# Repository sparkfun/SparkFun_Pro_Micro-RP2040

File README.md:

SparkFun Pro Micro RP2040
========================================

[*SparkFun Pro Micro RP2040 (DEV-17717)*](https://www.sparkfun.com/products/17717)

The SparkFun Pro Micro RP2040 is a low-cost, high performance board with flexible digital interfaces featuring the Raspberry Pi Foundation's RP2040 microcontroller. Besides the good 'ol Pro Micro footprint, the board also includes a WS2812B addressable LED, boot button, reset button, Qwiic connector, USB-C, resettable PTC fuse, and castellated pads.

Repository Contents
-------------------

* **/Hardware** - All Eagle design files (.brd, .sch, .STL)

Documentation
--------------

* **[Hookup Guide](https://learn.sparkfun.com/tutorials/1560)** - Basic hookup guide for the Pro Micro RP2040
* **[SparkFun Graphical Datasheets](https://github.com/sparkfun/Graphical_Datasheets)** - Graphical datasheets for various SparkFun products.

Product Versions
----------------

* [DEV-17717](https://www.sparkfun.com/products/17717)- initial release

License Information
-------------------

This product is _**open source**_! 

Please review the LICENSE.md file for license information. 

If you have any questions or concerns on licensing, please contact technical support on our [SparkFun forums](https://forum.sparkfun.com/viewforum.php?f=152).

Distributed as-is; no warranty is given.

- Your friends at SparkFun.

_<COLLABORATION CREDIT>_

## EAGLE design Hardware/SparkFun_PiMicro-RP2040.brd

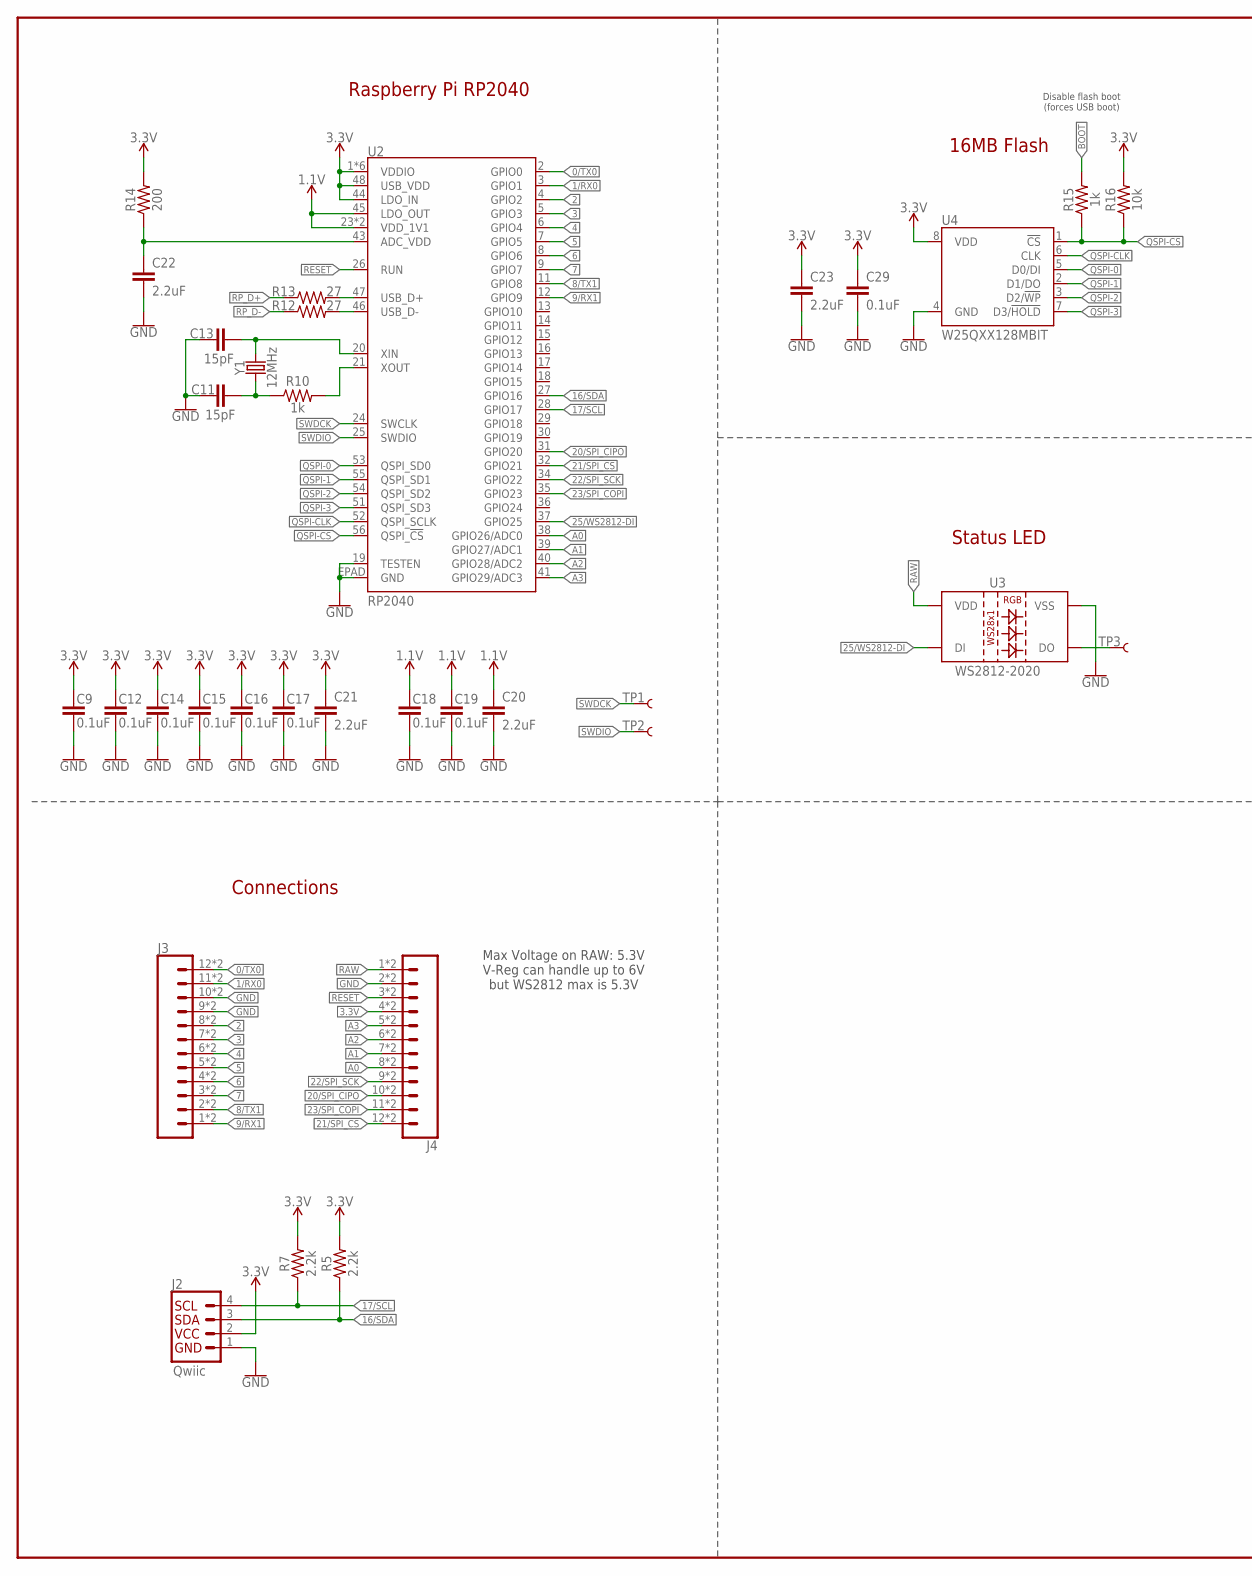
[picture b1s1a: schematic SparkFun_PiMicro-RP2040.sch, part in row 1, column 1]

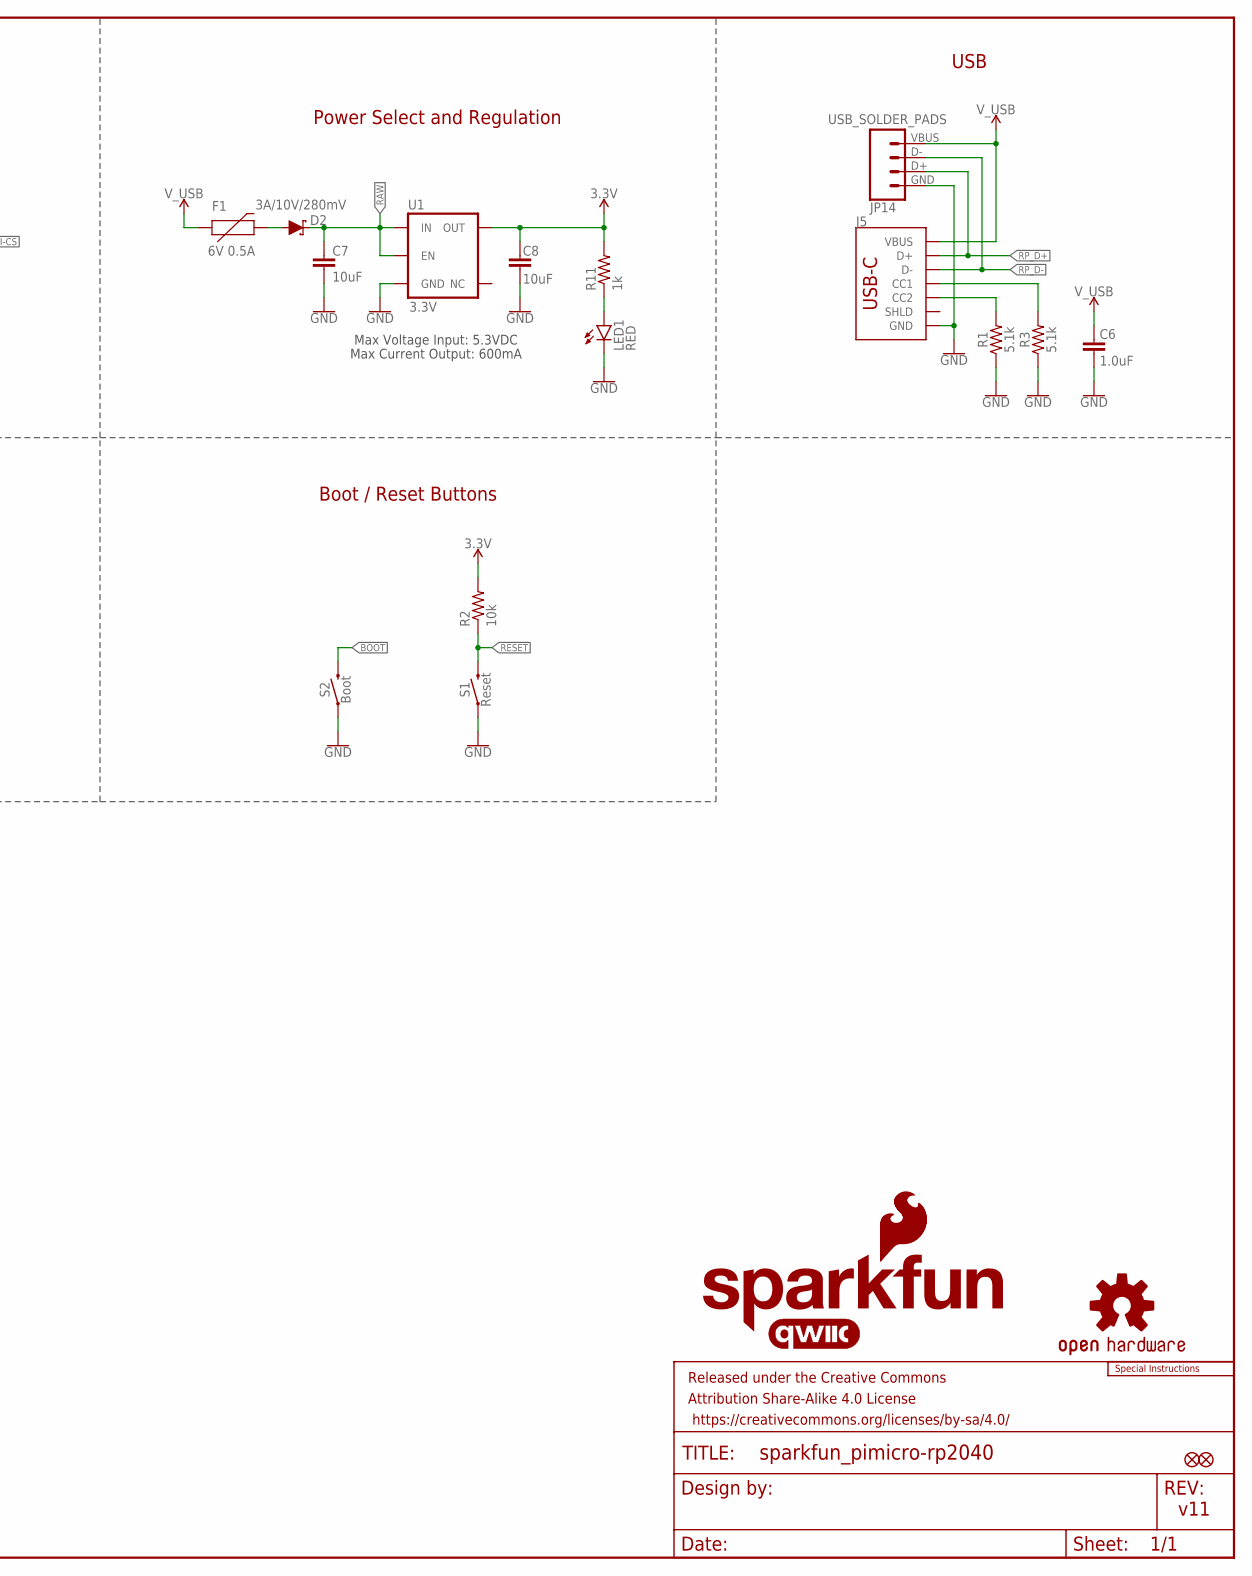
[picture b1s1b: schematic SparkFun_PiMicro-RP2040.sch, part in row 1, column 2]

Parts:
C6: 1.0uF; 0402-TIGHT
C7, C8: 10uF; 0402-TIGHT
C9, C12, C14, C15, C16, C17, C18, C19, C29: 0.1uF; 0402-TIGHT
C11, C13: 15pF; 0402-TIGHT
C20, C21, C22, C23: 2.2uF; 0402-TIGHT
D2: 3A/10V/280mV; SOD-323
F1: 6V 0.5A; 0805
FRAME2: FRAME-LEDGER; CREATIVE_COMMONS
J2: Qwiic; JST04_1MM_RA
J3, J4: CONN_12CASTLE; 1X12_CASTELLATED
J5: USB Female Type C Connector; USB-C-16P_4LAYER-PADS
JP1, JP2: FIDUCIAL1X2; FIDUCIAL-1X2
JP14: USB_SOLDER_PADS; USB-SOLDER-PADS
LED1: RED; LED-0603
LOGO1: SFE_LOGO_NAME_FLAME.1_INCH; SFE_LOGO_NAME_FLAME_.1
LOGO3: QWIIC_LOGO_6MM; QWIIC_6MM
LOGO4: SFE_LOGO_FLAME.1_INCH; SFE_LOGO_FLAME_.1
LOGO5: SPECIAL_INSTRUCTIONS-ORDERING; ORDERING_INSTRUCTIONS
R1, R3: 5.1k; 0402-TIGHT
R2, R16: 10k; 0402-TIGHT
R5, R7: 2.2k; 0402-TIGHT
R10, R11, R15: 1k; 0402-TIGHT
R12, R13: 27; 0402-TIGHT
R14: 200; 0402-TIGHT
S1: Reset; TACTILE_SWITCH_SMD_4.6X2.8MM
S2: Boot; TACTILE_SWITCH_SMD_4.6X2.8MM
TP1, TP2, TP3: TEST-POINT3X5; PAD.03X.05
U1: 3.3V; SOT23-5
U2: RP2040; QFN-56
U3: WS2812-2020
U4: W25QXX128MBIT; WSON-8-6X5-SKINNY_CENTERPAD
U$3: OSHW-LOGOMINI; OSHW-LOGO-MINI
Y1: 12MHz; CRYSTAL-SMD-2X2.5MM

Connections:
0/TX0: J3.12, J3.12B (12), U2.2 (GPIO0)
1.1V: C18.1, C19.1, C20.1, U2.23 (VDD_1V1), U2.45 (LDO_OUT), U2.50 (VDD_1V1)
1/RX0: J3.11, J3.11B (11), U2.3 (GPIO1)
2: J3.8, J3.8B (8), U2.4 (GPIO2)
3: J3.7, J3.7B (7), U2.5 (GPIO3)
3.3V: C8.2, C9.1, C12.1, C14.1, C15.1, C16.1, C17.1, C21.1, C23.1, C29.1, J2.2, J4.4, J4.4B (4), R2.2, R5.2, R7.2, R11.2, R14.2, R16.2, U1.5 (OUT), U2.1 (VDDIO), U2.10 (VDDIO), U2.22 (VDDIO), U2.33 (VDDIO), U2.42 (VDDIO), U2.44 (LDO_IN), U2.48 (USB_VDD), U2.49 (VDDIO), U4.8 (VDD)
4: J3.6, J3.6B (6), U2.6 (GPIO4)
5: J3.5, J3.5B (5), U2.7 (GPIO5)
6: J3.4, J3.4B (4), U2.8 (GPIO6)
7: J3.3, J3.3B (3), U2.9 (GPIO7)
8/TX1: J3.2, J3.2B (2), U2.11 (GPIO8)
9/RX1: J3.1, J3.1B (1), U2.12 (GPIO9)
16/SDA: J2.3, R5.1, U2.27 (GPIO16)
17/SCL: J2.4, R7.1, U2.28 (GPIO17)
20/SPI_CIPO: J4.10, J4.10B (10), U2.31 (GPIO20)
21/SPI_!CS!: J4.12, J4.12B (12), U2.32 (GPIO21)
22/SPI_SCK: J4.9, J4.9B (9), U2.34 (GPIO22)
23/SPI_COPI: J4.11, J4.11B (11), U2.35 (GPIO23)
25/WS2812-DI: U2.37 (GPIO25), U3.3 (DI)
!RESET!: J4.3, J4.3B (3), R2.1, S1.3 (2), S1.4 (2), U2.26 (RUN)
A0: J4.8, J4.8B (8), U2.38 (GPIO26/ADC0)
A1: J4.7, J4.7B (7), U2.39 (GPIO27/ADC1)
A2: J4.6, J4.6B (6), U2.40 (GPIO28/ADC2)
A3: J4.5, J4.5B (5), U2.41 (GPIO29/ADC3)
ADC_VDD: C22.1, R14.1, U2.43 (ADC_VDD)
BOOT: R15.2, S2.3 (2), S2.4 (2)
GND: C6.1, C7.1, C8.1, C9.2, C11.1, C12.2, C13.1, C14.2, C15.2, C16.2, C17.2, C18.2, C19.2, C20.2, C21.2, C22.2, C23.2, C29.2, J2.1, J3.9, J3.9B (9), J3.10, J3.10B (10), J4.2, J4.2B (2), J5.GND, J5.GND2 (GND), JP14.GND (4), LED1.C, R1.1, R3.1, S1.1, S1.2 (1), S2.1, S2.2 (1), U1.2 (GND), U2.19 (TESTEN), U2.EPAD (GND), U3.2 (VSS), U4.4 (GND)
unnamed: TP3.P$1, U3.1 (DO)
unnamed: J5.A5 (CC1), R3.2
unnamed: J5.B5 (CC2), R1.2
unnamed: LED1.A, R11.1
QSPI-0: U2.53 (QSPI_SD0), U4.5 (D0/DI)
QSPI-1: U2.55 (QSPI_SD1), U4.2 (D1/DO)
QSPI-2: U2.54 (QSPI_SD2), U4.3 (D2/!WP!)
QSPI-3: U2.51 (QSPI_SD3), U4.7 (D3/!HOLD!)
QSPI-CLK: U2.52 (QSPI_SCLK), U4.6 (CLK)
QSPI-CS: R15.1, R16.1, U2.56 (QSPI_!CS!), U4.1 (!CS!)
RAW: C7.2, D2.C, J4.1, J4.1B (1), U1.1 (IN), U1.3 (EN), U3.4 (VDD)
RP_D1+: R13.2, U2.47 (USB_D+)
RP_D1-: R12.2, U2.46 (USB_D-)
RP_D+: J5.A6 (D+), J5.B6 (D+), JP14.D+ (3), R13.1
RP_D-: J5.A7 (D-), J5.B7 (D-), JP14.D- (2), R12.1
SWDCK: TP1.P$1, U2.24 (SWCLK)
SWDIO: TP2.P$1, U2.25 (SWDIO)
USB_RAW: D2.A, F1.2
V_USB: C6.2, F1.1, J5.VBUS1 (VBUS), J5.VBUS2 (VBUS), JP14.VBUS (1)
X1A: R10.2, U2.21 (XOUT)
X1B: C11.2, R10.1, Y1.P1 (1)
X2: C13.2, U2.20 (XIN), Y1.P3 (2)

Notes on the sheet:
Max Voltage Input: 5.3VDC
Max Current Output: 600mA
v11
Raspberry Pi RP2040
16MB Flash
Disable flash boot (forces USB boot)
Status LED
Power Select and Regulation
USB
Connections
Boot / Reset Buttons
Max Voltage on RAW: 5.3V V-Reg can handle up to 6V but WS2812 max is 5.3V

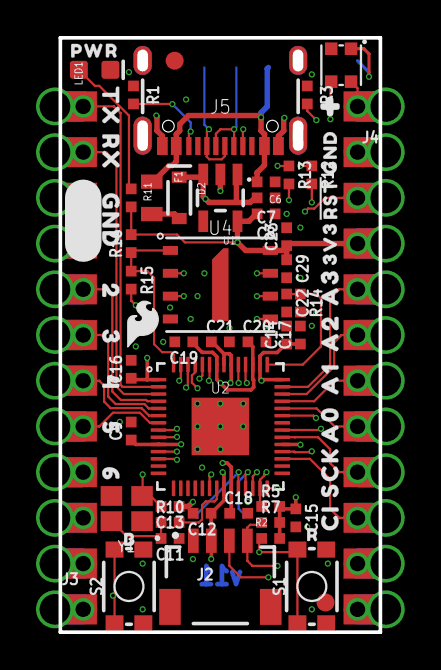
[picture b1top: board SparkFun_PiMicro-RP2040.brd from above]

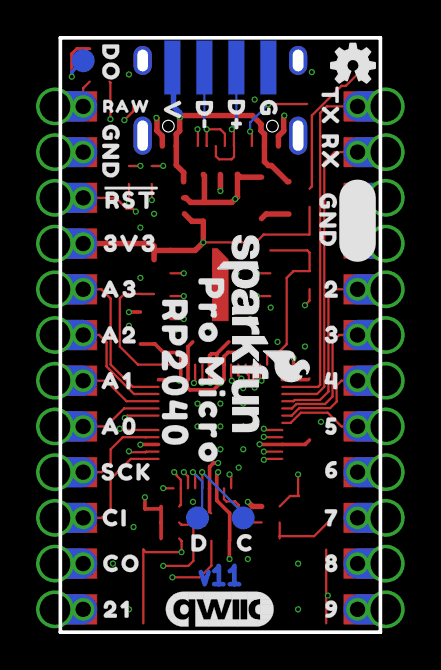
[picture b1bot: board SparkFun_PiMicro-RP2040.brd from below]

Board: 4 copper layers, 17.8 x 33.0 mm, 109 parts (39 on the bottom side), 49 nets.

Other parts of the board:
U$1, U$11: A00
U$2: GND_0
U$4: PRO_MICRO0
U$5: #0
U$6: 70
U$7: 81
U$8: 92
U$9, U$64: CI4
U$10, U$67: SCK3
U$12, U$20: A10
U$13, U$33: A21
U$14, U$39: A32
U$15, U$22, U$74: GND2
U$16: 3V3_0
U$17: RAW0
U$18: C0
U$19, U$76: TX0
U$21, U$75: RX1
U$23, U$53: 20
U$24, U$54: 31
U$25, U$55: 42
U$26, U$56: 53
U$27, U$57: 64
U$28: D#1
U$29: D#2
U$30: G0
U$31: V3
U$32: 210
U$34: #RST#0
U$35: D1
U$36: B0
U$37: R0
U$38: RP20401
U$40: DO0
U$66: CO5
U$68: #RST#1
U$69: 3V30
U$73: PWR0

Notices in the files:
parts and their libraries:
SparkFun-Aesthetics: Licensing: CC v3.0 Share-Alike You are welcome to use this library for commercial purposes.
SparkFun-IC-Power: Licensing: Creative Commons ShareAlike 4.0 International - https://creativecommons.org/licenses/by-sa/4.0
SparkFun-Aesthetics: Released under the Creative Commons
